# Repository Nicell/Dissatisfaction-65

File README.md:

# Dissatisfaction65
<center>
  
</center>
This is the hardware repository for my 65% QMK Bluetooth keyboard with an OLED and encoder.

**I'm working on a new version of this to vastly improve the design and functionality. You can follow the development on [this discord](https://discord.gg/mYy7CFR)**

# Software (QMK)
You can currently find the firmware for this board at [my qmk-firmware fork](https://github.com/Nicell/qmk_firmware/tree/dissatisfaction-65). It requires [this pull-request](https://github.com/qmk/qmk_firmware/pull/7769) before it can be fully upstreamed.

# What you'll need (or at least what I used)
You can get most of these items at different places, but I left the more convenient places here. Often you can get cheaper electronics at LCSC and AliExpress rather than Mouser and Amazon.
 - Adafruit Feather 32u4 Bluefruit LE [BUY](https://www.amazon.com/Adafruit-Feather-32u4-Bluefruit-ADA2829/dp/B01GJR9MNI)
 - 2500mAH battery or equivalent (probably don't go thicker) [BUY](https://www.amazon.com/Adafruit-328-Battery-Lithium-Polymer/dp/B01NAX9XYG)
 - EC12 Encoder Knob [BUY](https://www.amazon.com/Cylewet-Encoder-Digital-Potentiometer-Arduino/dp/B07DM2YMT4)
 - OLED SSD1306 128x32 [BUY](https://www.amazon.com/MakerFocus-Display-SSD1306-3-3V-5V-Arduino/dp/B079BN2J8V)
 - Long headers for the OLED to reach far down [BUY](https://www.mouser.com/ProductDetail/fci-amphenol/68653-105hlf)
 - 1N4148 DO-35 package 67x [BUY](https://www.mouser.com/ProductDetail/on-semiconductor/1n4148tr)
 - 74HC4515 Decoder [BUY](https://www.mouser.com/ProductDetail/nexperia/74hc4515d653)
 - On-Off switch [BUY](https://www.mouser.com/ProductDetail/alps/sddjf1a100)
 - Encoder Knob [BUY](https://www.amazon.com/dp/B07Z1MQ9T7)
 - M3 ([Bolts](https://www.amazon.com/gp/product/B075CFBHWV)) ([Nuts](https://www.amazon.com/gp/product/B01IWUSDYY)) ([Lock Nuts](https://www.amazon.com/gp/product/B07MD7SPBJ)) ([Rubber Feet](https://www.amazon.com/gp/product/B07CNQC695))
 - Plates: one of each of the plates found in the DXF folder. Middle MUST be 1.5mm. I got mine from SendCutSend in brushed stainless steel using the combined plates file. I highly recommend them. Fast, affordable, and good quality.
 - Middle pieces: 7x of the middle piece found in the DXF folder. I used 1/8in thick pieces. 2x between the top and switch plate, and 5x between the bottom and switch plate. The second and third to last from the bottom pieces need cutouts for both the micro USB and the power switch. I got mine from Sculpteo. I would not recommend them. The wait was long, the order was messed up, and the quality was very mediocre. There was an obvious taper on the cuts.
 - MX style switches 67x. PCB or plate mount
 - Keycaps! KLE can be found [here](http://www.keyboard-layout-editor.com/#/gists/c38820c1ede8c90e253ba465600c6e75).

# Things I'd like to change
There were a few things that I'd like to change. I haven't done them yet, but they would enhance the board.
 - Move the encoder switch to the matrix. Currently has its own direct connection.
 - Recreate the switch plate using ai03's plate designer. Currently has huge lines across stabs and the stab holes are really tight.
 - Re-dimension the OLED. It seems to be barely too far down and to the left. I can re-dimension now that I have calipers.
 - Redo the decoder using a 74HC154. No need to use the latched version that's more expensive and slower.
 - Create a little cut in the middle pieces to use as a prop up for the OLED.
 - Create pre-made middle pieces with cutouts for the micro USB port and the on-off switch rather than cutting them manually.

# Random things I encountered
 - Make sure to test your Adafruit board fully before soldering it in. The board I got had a working MCU and Bluetooth module, but they couldn't communicate properly despite continuity between the SPI pins.
 - My plate ended up flexing a bit when connecting the switches. I suspect the PCB was either a bit too small or the plate was a bit too big. I really don't know why this was the case.

# Thanks to
 - QMK team for helping me with getting the firmware working
 - Nick_68 and WoodKeys for each of their iterations on the Bluetooth + decoder design with the Ronin and Meira, which were invaluable for me while I was designing this board.
 - ai03 for the MX KiCad library I have in this project.

# Images

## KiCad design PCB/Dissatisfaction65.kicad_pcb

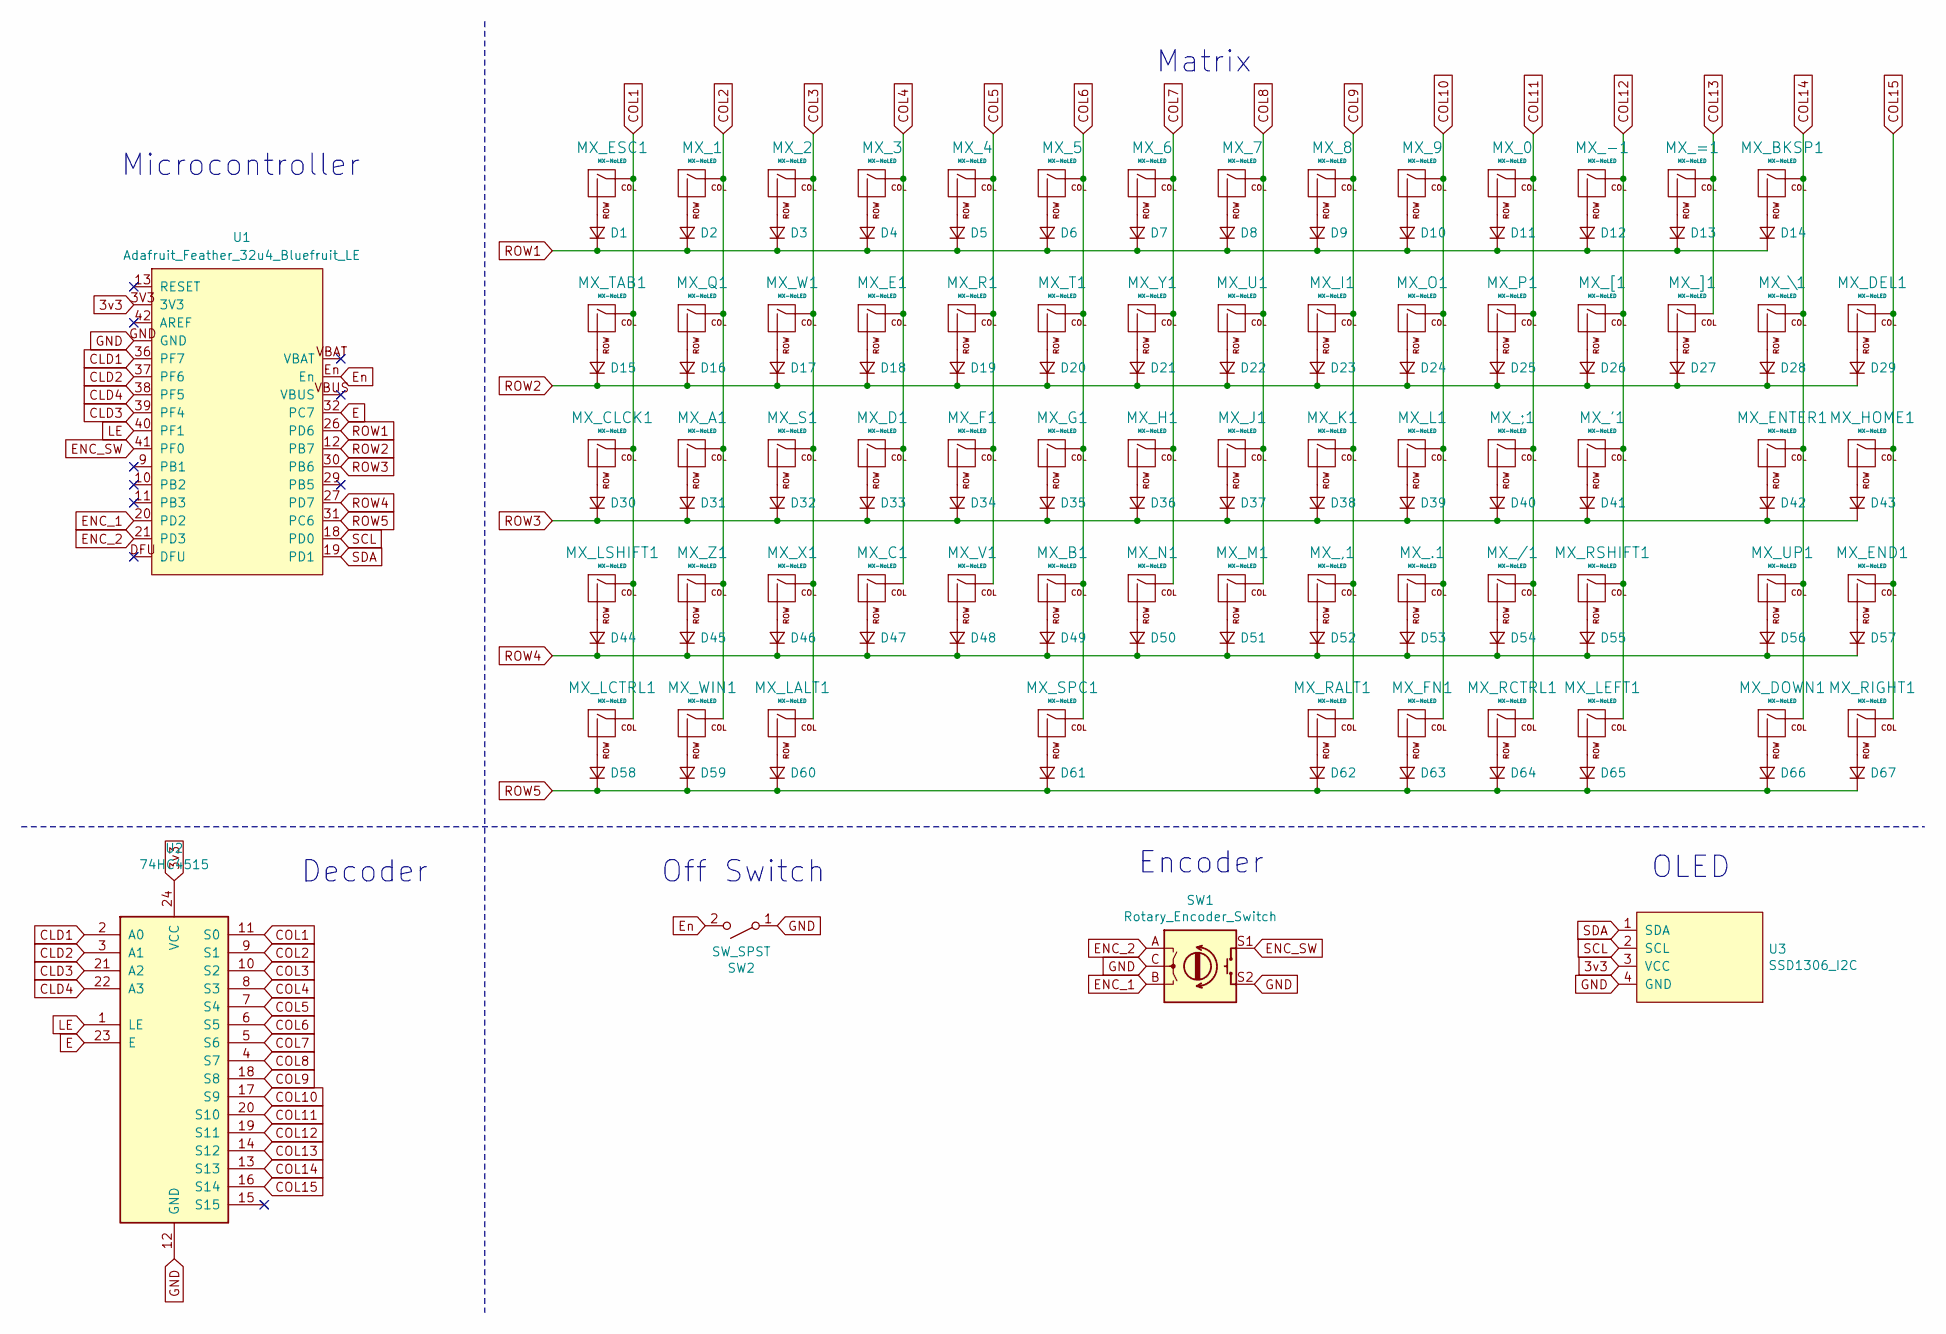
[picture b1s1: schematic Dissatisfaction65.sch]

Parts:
D1, D2, D3, D4, D5, D6, D7, D8, D9, D10, D11, D12, D13, D14, D15, D16, D17, D18, D19, D20, D21, D22, D23, D24, D25, D26, D27, D28, D29, D30, D31, D32, D33, D34, D35, D36, D37, D38, D39, D40, D41, D42, D43, D44, D45, D46, D47, D48, D49, D50, D51, D52, D53, D54, D55, D56, D57, D58, D59, D60, D61, D62, D63, D64, D65, D66, D67: D_Small; D_DO-35_SOD27_P7.62mm_Horizontal
MX_0, MX_1, MX_2, MX_3, MX_4, MX_5, MX_6, MX_7, MX_8, MX_9, MX_.1: MX-NoLED; MXOnly-1U-NoLED
MX_'1: MX-NoLED; MXOnly-1U-NoLED
MX_,1: MX-NoLED; MXOnly-1U-NoLED
MX_-1: MX-NoLED; MXOnly-1U-NoLED
MX_/1: MX-NoLED; MXOnly-1U-NoLED
MX_;1: MX-NoLED; MXOnly-1U-NoLED
MX_=1: MX-NoLED; MXOnly-1U-NoLED
MX_A1: MX-NoLED; MXOnly-1U-NoLED
MX_B1: MX-NoLED; MXOnly-1U-NoLED
MX_BKSP1: MX-NoLED; MXOnly-2U-NoLED
MX_C1: MX-NoLED; MXOnly-1U-NoLED
MX_CLCK1: MX-NoLED; MXOnly-1.75U-NoLED
MX_D1: MX-NoLED; MXOnly-1U-NoLED
MX_DEL1: MX-NoLED; MXOnly-1U-NoLED
MX_DOWN1: MX-NoLED; MXOnly-1U-NoLED
MX_E1: MX-NoLED; MXOnly-1U-NoLED
MX_END1: MX-NoLED; MXOnly-1U-NoLED
MX_ENTER1: MX-NoLED; MXOnly-2.25U-NoLED
MX_ESC1: MX-NoLED; MXOnly-1U-NoLED
MX_F1: MX-NoLED; MXOnly-1U-NoLED
MX_FN1: MX-NoLED; MXOnly-1U-NoLED
MX_G1: MX-NoLED; MXOnly-1U-NoLED
MX_H1: MX-NoLED; MXOnly-1U-NoLED
MX_HOME1: MX-NoLED; MXOnly-1U-NoLED
MX_I1: MX-NoLED; MXOnly-1U-NoLED
MX_J1: MX-NoLED; MXOnly-1U-NoLED
MX_K1: MX-NoLED; MXOnly-1U-NoLED
MX_L1: MX-NoLED; MXOnly-1U-NoLED
MX_LALT1: MX-NoLED; MXOnly-1.25U-NoLED
MX_LCTRL1: MX-NoLED; MXOnly-1.25U-NoLED
MX_LEFT1: MX-NoLED; MXOnly-1U-NoLED
MX_LSHIFT1: MX-NoLED; MXOnly-2.25U-NoLED
MX_M1: MX-NoLED; MXOnly-1U-NoLED
MX_N1: MX-NoLED; MXOnly-1U-NoLED
MX_O1: MX-NoLED; MXOnly-1U-NoLED
MX_P1: MX-NoLED; MXOnly-1U-NoLED
MX_Q1: MX-NoLED; MXOnly-1U-NoLED
MX_R1: MX-NoLED; MXOnly-1U-NoLED
MX_RALT1: MX-NoLED; MXOnly-1U-NoLED
MX_RCTRL1: MX-NoLED; MXOnly-1U-NoLED
MX_RIGHT1: MX-NoLED; MXOnly-1U-NoLED
MX_RSHIFT1: MX-NoLED; MXOnly-1.75U-NoLED
MX_S1: MX-NoLED; MXOnly-1U-NoLED
MX_SPC1: MX-NoLED; MXOnly-6.25U-ReversedStabilizers-NoLED
MX_T1: MX-NoLED; MXOnly-1U-NoLED
MX_TAB1: MX-NoLED; MXOnly-1.5U-NoLED
MX_U1: MX-NoLED; MXOnly-1U-NoLED
MX_UP1: MX-NoLED; MXOnly-1U-NoLED
MX_V1: MX-NoLED; MXOnly-1U-NoLED
MX_W1: MX-NoLED; MXOnly-1U-NoLED
MX_WIN1: MX-NoLED; MXOnly-1.25U-NoLED
MX_X1: MX-NoLED; MXOnly-1U-NoLED
MX_Y1: MX-NoLED; MXOnly-1U-NoLED
MX_Z1: MX-NoLED; MXOnly-1U-NoLED
MX_[1: MX-NoLED; MXOnly-1U-NoLED
MX_\1: MX-NoLED; MXOnly-1.5U-NoLED
MX_]1: MX-NoLED; MXOnly-1U-NoLED
SW1: Rotary_Encoder_Switch; RotaryEncoder_Alps_EC11E-Switch_Vertical_H20mm
SW2: SW_SPST; PinHeader_1x02_P2.54mm_Vertical
U1: Adafruit_Feather_32u4_Bluefruit_LE
U2: 74HC4515; SOIC-24W_7.5x15.4mm_P1.27mm
U3: SSD1306_I2C; OLED

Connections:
3v3: U1.3V3, U2.24 (VCC), U3.3 (VCC)
CLD1: U1.36 (PF7), U2.2 (A0)
CLD2: U1.37 (PF6), U2.3 (A1)
CLD3: U1.39 (PF4), U2.21 (A2)
CLD4: U1.38 (PF5), U2.22 (A3)
COL1: MX_CLCK1.1 (COL), MX_ESC1.1 (COL), MX_LCTRL1.1 (COL), MX_LSHIFT1.1 (COL), MX_TAB1.1 (COL), U2.11 (S0)
COL2: MX_1.1 (COL), MX_A1.1 (COL), MX_Q1.1 (COL), MX_WIN1.1 (COL), MX_Z1.1 (COL), U2.9 (S1)
COL3: MX_2.1 (COL), MX_LALT1.1 (COL), MX_S1.1 (COL), MX_W1.1 (COL), MX_X1.1 (COL), U2.10 (S2)
COL4: MX_3.1 (COL), MX_C1.1 (COL), MX_D1.1 (COL), MX_E1.1 (COL), U2.8 (S3)
COL5: MX_4.1 (COL), MX_F1.1 (COL), MX_R1.1 (COL), MX_V1.1 (COL), U2.7 (S4)
COL6: MX_5.1 (COL), MX_B1.1 (COL), MX_G1.1 (COL), MX_SPC1.1 (COL), MX_T1.1 (COL), U2.6 (S5)
COL7: MX_6.1 (COL), MX_H1.1 (COL), MX_N1.1 (COL), MX_Y1.1 (COL), U2.5 (S6)
COL8: MX_7.1 (COL), MX_J1.1 (COL), MX_M1.1 (COL), MX_U1.1 (COL), U2.4 (S7)
COL9: MX_8.1 (COL), MX_,1.1 (COL), MX_I1.1 (COL), MX_K1.1 (COL), MX_RALT1.1 (COL), U2.18 (S8)
COL10: MX_9.1 (COL), MX_.1.1 (COL), MX_FN1.1 (COL), MX_L1.1 (COL), MX_O1.1 (COL), U2.17 (S9)
COL11: MX_0.1 (COL), MX_/1.1 (COL), MX_;1.1 (COL), MX_P1.1 (COL), MX_RCTRL1.1 (COL), U2.20 (S10)
COL12: MX_'1.1 (COL), MX_-1.1 (COL), MX_LEFT1.1 (COL), MX_RSHIFT1.1 (COL), MX_[1.1 (COL), U2.19 (S11)
COL13: MX_=1.1 (COL), MX_]1.1 (COL), U2.14 (S12)
COL14: MX_BKSP1.1 (COL), MX_DOWN1.1 (COL), MX_ENTER1.1 (COL), MX_UP1.1 (COL), MX_\1.1 (COL), U2.13 (S13)
COL15: MX_DEL1.1 (COL), MX_END1.1 (COL), MX_HOME1.1 (COL), MX_RIGHT1.1 (COL), U2.16 (S14)
E: U1.32 (PC7), U2.23 (E)
ENC_1: SW1.B, U1.20 (PD2)
ENC_2: SW1.A, U1.21 (PD3)
ENC_SW: SW1.S1, U1.41 (PF0)
En: SW2.2 (B), U1.En
GND: SW1.C, SW1.S2, SW2.1 (A), U1.GND, U2.12 (GND), U3.4 (GND)
LE: U1.40 (PF1), U2.1 (LE)
unnamed: D1.2 (A), MX_ESC1.2 (ROW)
unnamed: D2.2 (A), MX_1.2 (ROW)
unnamed: D3.2 (A), MX_2.2 (ROW)
unnamed: D4.2 (A), MX_3.2 (ROW)
unnamed: D5.2 (A), MX_4.2 (ROW)
unnamed: D6.2 (A), MX_5.2 (ROW)
unnamed: D7.2 (A), MX_6.2 (ROW)
unnamed: D8.2 (A), MX_7.2 (ROW)
unnamed: D9.2 (A), MX_8.2 (ROW)
unnamed: D10.2 (A), MX_9.2 (ROW)
unnamed: D11.2 (A), MX_0.2 (ROW)
unnamed: D12.2 (A), MX_-1.2 (ROW)
unnamed: D13.2 (A), MX_=1.2 (ROW)
unnamed: D14.2 (A), MX_BKSP1.2 (ROW)
unnamed: D15.2 (A), MX_TAB1.2 (ROW)
unnamed: D16.2 (A), MX_Q1.2 (ROW)
unnamed: D17.2 (A), MX_W1.2 (ROW)
unnamed: D18.2 (A), MX_E1.2 (ROW)
unnamed: D19.2 (A), MX_R1.2 (ROW)
unnamed: D20.2 (A), MX_T1.2 (ROW)
unnamed: D21.2 (A), MX_Y1.2 (ROW)
unnamed: D22.2 (A), MX_U1.2 (ROW)
unnamed: D23.2 (A), MX_I1.2 (ROW)
unnamed: D24.2 (A), MX_O1.2 (ROW)
unnamed: D25.2 (A), MX_P1.2 (ROW)
unnamed: D26.2 (A), MX_[1.2 (ROW)
unnamed: D27.2 (A), MX_]1.2 (ROW)
unnamed: D28.2 (A), MX_\1.2 (ROW)
unnamed: D29.2 (A), MX_DEL1.2 (ROW)
unnamed: D30.2 (A), MX_CLCK1.2 (ROW)
unnamed: D31.2 (A), MX_A1.2 (ROW)
unnamed: D32.2 (A), MX_S1.2 (ROW)
unnamed: D33.2 (A), MX_D1.2 (ROW)
unnamed: D34.2 (A), MX_F1.2 (ROW)
unnamed: D35.2 (A), MX_G1.2 (ROW)
unnamed: D36.2 (A), MX_H1.2 (ROW)
unnamed: D37.2 (A), MX_J1.2 (ROW)
unnamed: D38.2 (A), MX_K1.2 (ROW)
unnamed: D39.2 (A), MX_L1.2 (ROW)
unnamed: D40.2 (A), MX_;1.2 (ROW)
unnamed: D41.2 (A), MX_'1.2 (ROW)
unnamed: D42.2 (A), MX_ENTER1.2 (ROW)
unnamed: D43.2 (A), MX_HOME1.2 (ROW)
unnamed: D44.2 (A), MX_LSHIFT1.2 (ROW)
unnamed: D45.2 (A), MX_Z1.2 (ROW)
unnamed: D46.2 (A), MX_X1.2 (ROW)
unnamed: D47.2 (A), MX_C1.2 (ROW)
unnamed: D48.2 (A), MX_V1.2 (ROW)
unnamed: D49.2 (A), MX_B1.2 (ROW)
unnamed: D50.2 (A), MX_N1.2 (ROW)
unnamed: D51.2 (A), MX_M1.2 (ROW)
unnamed: D52.2 (A), MX_,1.2 (ROW)
unnamed: D53.2 (A), MX_.1.2 (ROW)
unnamed: D54.2 (A), MX_/1.2 (ROW)
unnamed: D55.2 (A), MX_RSHIFT1.2 (ROW)
unnamed: D56.2 (A), MX_UP1.2 (ROW)
unnamed: D57.2 (A), MX_END1.2 (ROW)
unnamed: D58.2 (A), MX_LCTRL1.2 (ROW)
unnamed: D59.2 (A), MX_WIN1.2 (ROW)
unnamed: D60.2 (A), MX_LALT1.2 (ROW)
unnamed: D61.2 (A), MX_SPC1.2 (ROW)
unnamed: D62.2 (A), MX_RALT1.2 (ROW)
unnamed: D63.2 (A), MX_FN1.2 (ROW)
unnamed: D64.2 (A), MX_RCTRL1.2 (ROW)
unnamed: D65.2 (A), MX_LEFT1.2 (ROW)
unnamed: D66.2 (A), MX_DOWN1.2 (ROW)
unnamed: D67.2 (A), MX_RIGHT1.2 (ROW)
ROW1: D1.1 (K), D2.1 (K), D3.1 (K), D4.1 (K), D5.1 (K), D6.1 (K), D7.1 (K), D8.1 (K), D9.1 (K), D10.1 (K), D11.1 (K), D12.1 (K), D13.1 (K), D14.1 (K), U1.26 (PD6)
ROW2: D15.1 (K), D16.1 (K), D17.1 (K), D18.1 (K), D19.1 (K), D20.1 (K), D21.1 (K), D22.1 (K), D23.1 (K), D24.1 (K), D25.1 (K), D26.1 (K), D27.1 (K), D28.1 (K), D29.1 (K), U1.12 (PB7)
ROW3: D30.1 (K), D31.1 (K), D32.1 (K), D33.1 (K), D34.1 (K), D35.1 (K), D36.1 (K), D37.1 (K), D38.1 (K), D39.1 (K), D40.1 (K), D41.1 (K), D42.1 (K), D43.1 (K), U1.30 (PB6)
ROW4: D44.1 (K), D45.1 (K), D46.1 (K), D47.1 (K), D48.1 (K), D49.1 (K), D50.1 (K), D51.1 (K), D52.1 (K), D53.1 (K), D54.1 (K), D55.1 (K), D56.1 (K), D57.1 (K), U1.27 (PD7)
ROW5: D58.1 (K), D59.1 (K), D60.1 (K), D61.1 (K), D62.1 (K), D63.1 (K), D64.1 (K), D65.1 (K), D66.1 (K), D67.1 (K), U1.31 (PC6)
SCL: U1.18 (PD0), U3.2 (SCL)
SDA: U1.19 (PD1), U3.1 (SDA)

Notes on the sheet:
Matrix
Decoder
Microcontroller
Off Switch
Encoder
OLED

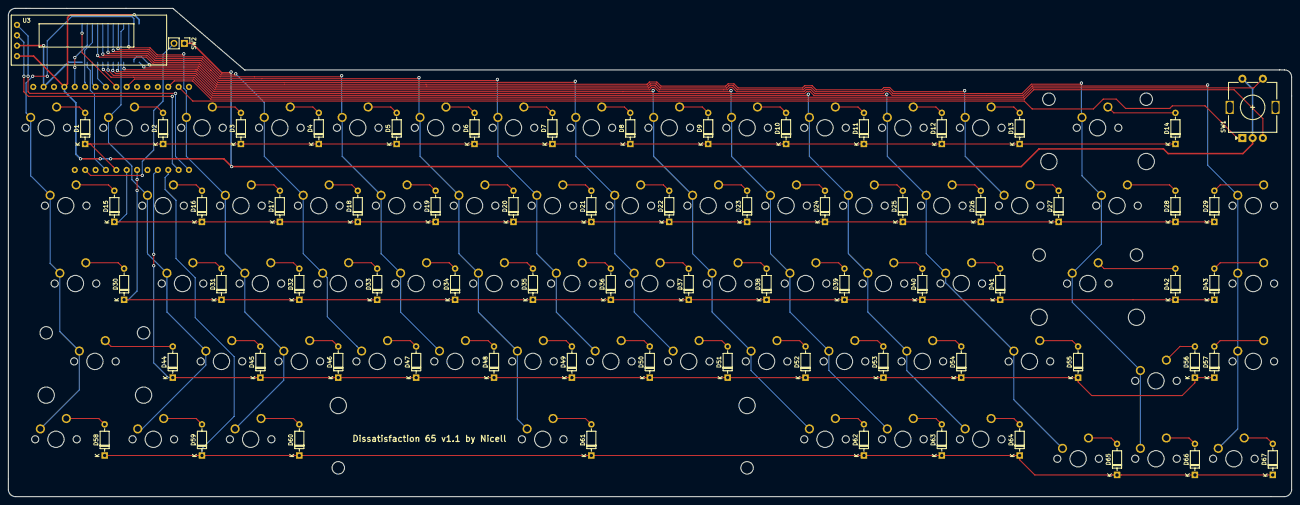
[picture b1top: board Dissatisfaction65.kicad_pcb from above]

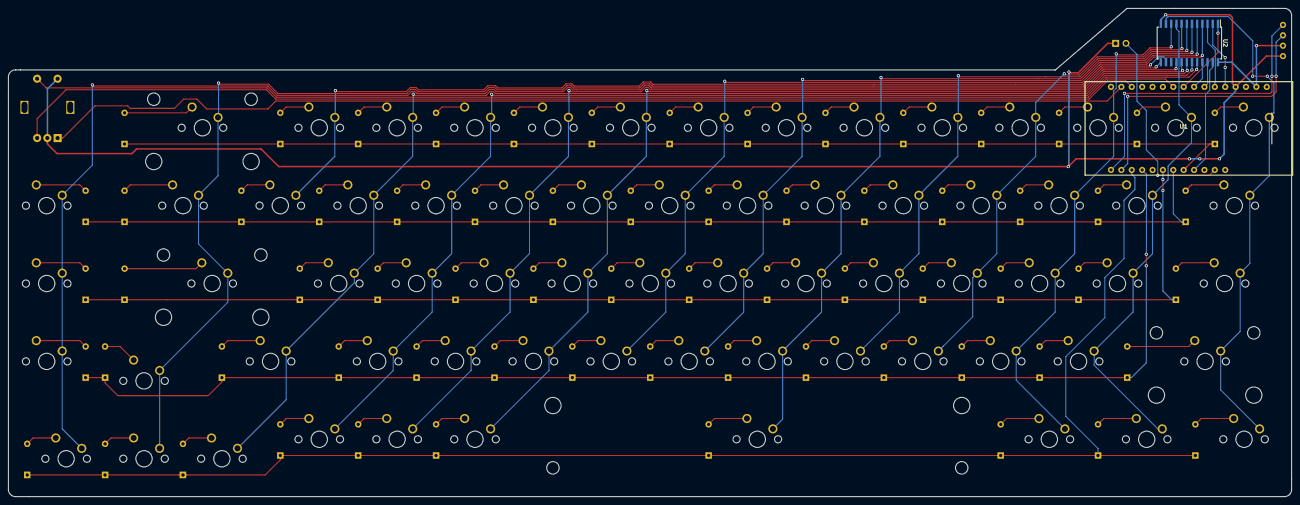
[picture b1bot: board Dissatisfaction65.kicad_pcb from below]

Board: 2 copper layers, 313.9 x 119.4 mm, 139 parts (2 on the bottom side), 101 nets.

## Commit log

2020-02-09 Typos and Discord
